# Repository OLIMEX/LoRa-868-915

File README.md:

# LoRa868 / LoRa915 / MOD-LoRa868 / MOD-LoRa915

LoRa modules with SX1276 modem from Semtech.

Product page: https://www.olimex.com/Products/IoT/LoRa/LoRa868/open-source-hardware

Product page: https://www.olimex.com/Products/IoT/LoRa/LoRa915/open-source-hardware

Product page: https://www.olimex.com/Products/IoT/LoRa/MOD-LoRa868/open-source-hardware

Product page: https://www.olimex.com/Products/IoT/LoRa/MOD-LoRa915/open-source-hardware

## License
* Hardware design is released under CERN OHL v1.2 license
* Software is released under GPL3 License
* Documentation is released under CC BY-SA 3.0

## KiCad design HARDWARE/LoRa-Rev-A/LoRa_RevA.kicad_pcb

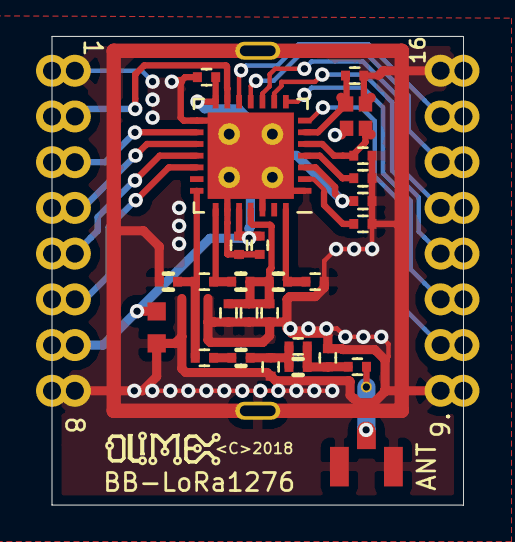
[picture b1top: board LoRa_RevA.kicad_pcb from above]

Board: 2 copper layers, 22.9 x 26.0 mm, 31 parts (0 on the bottom side), 25 nets.

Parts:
C1, C2: 15pF; C_0402_5MIL_DWS
C3, C4, C5, C6, C20: 100nF; C_0402_5MIL_DWS
C7, C8, C16, C21: 47pF; C_0402_5MIL_DWS
C9: 33pF; C_0402_5MIL_DWS
C10: 22uF; C_0603_5MIL_DWS
C11: 4.7pF; C_0402_5MIL_DWS
C12: 1.2pF; C_0402_5MIL_DWS
C13: 1.8pF; C_0402_5MIL_DWS
C19: 2.2pF; C_0402_5MIL_DWS
C25: n.a. (2.2pF); C_0402_5MIL_DWS
C36: 10nF; C_0402_5MIL_DWS
CON1, CON2: CON8; HN1x8_EDGE
EXT_ANT1: U.FL; U.FL-R-SMT-1
JANT1: TESTPAD; TP_SMD
L1: n.a. (82nH); L_0402_5MIL_DWS
L2: 33nH; L_0402_5MIL_DWS
L3: 6.8nH; L_0402_5MIL_DWS
L4: 10nH; L_0402_5MIL_DWS
L5: 6.2nH; L_0402_5MIL_DWS
SHIELD1: TESTPAD; Shield1620
U1: SX1276; QFN-28_EP_6x6_Pitch0.65mm
X1: 32.000MHz_10ppm; SMD2016_4p

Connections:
/DIO0: CON2.6, U1.8
/DIO1: CON2.5, U1.9
/DIO2: CON2.4, U1.10
/DIO3: CON2.3, U1.11
/DIO4: CON2.2, U1.12
/DIO5: CON1.7, U1.13
/MISO: CON1.5, U1.17
/MOSI: CON1.4, U1.18
/NSS: CON1.3, U1.19
/RESET: CON2.7, U1.7
/SCK: CON1.6, U1.16
GND: C1.2, C2.2, C3.2, C4.2, C5.2, C6.2, C7.1, C8.1, C10.2, C11.2, C13.2, C20.2, C21.2, C25.1, C36.2, CON1.1, CON1.8, CON2.1, CON2.8, EXT_ANT1.2, L3.1, SHIELD1.1, U1.1, U1.15, U1.23, U1.26, U1.29, X1.2, X1.4
unnamed: C1.1, U1.6, X1.1
unnamed: C2.1, U1.5, X1.3
unnamed: C4.1, U1.2
unnamed: C5.1, U1.4
unnamed: C9.1, L4.1
unnamed: C11.1, C12.2, L4.2, L5.1
unnamed: C12.1, C13.1, C16.2, L5.2
unnamed: C16.1, EXT_ANT1.1, JANT1.1
unnamed: C9.2, C19.1, L3.2, U1.21
unnamed: C19.2, L2.1, U1.22
unnamed: C25.2, L1.1, U1.28
unnamed: C7.2, C8.2, C36.1, L1.2, L2.2, U1.25
VAA: C3.1, C6.1, C10.1, C20.1, C21.1, CON1.2, U1.3, U1.14, U1.24

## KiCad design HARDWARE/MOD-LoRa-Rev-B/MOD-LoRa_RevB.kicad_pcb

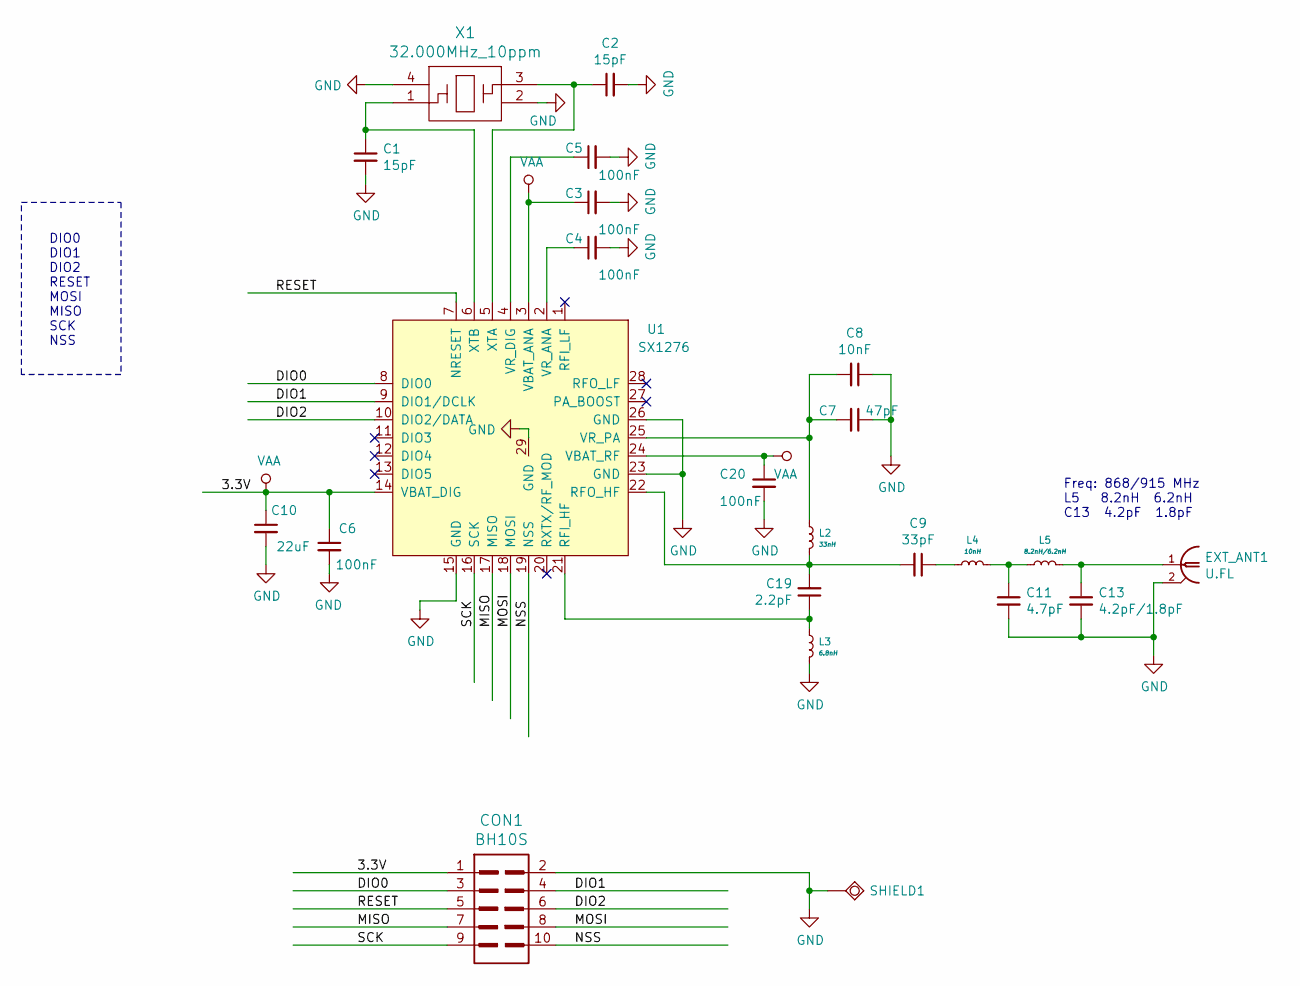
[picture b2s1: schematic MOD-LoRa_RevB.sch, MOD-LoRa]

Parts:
C1, C2: 15pF; C_0402_5MIL_DWS
C3, C4, C5, C6, C20: 100nF; C_0402_5MIL_DWS
C7: 47pF; C_0402_5MIL_DWS
C8: 10nF; C_0402_5MIL_DWS
C9: 33pF; C_0402_5MIL_DWS
C10: 22uF; C_0603_5MIL_DWS
C11: 4.7pF; C_0402_5MIL_DWS
C13: 4.2pF/1.8pF; C_0402_5MIL_DWS
C19: 2.2pF; C_0402_5MIL_DWS
CON1: BH10S; UEXTF
EXT_ANT1: U.FL; U.FL-R-SMT-1
L2: 33nH; L_0402_5MIL_DWS
L3: 6.8nH; L_0402_5MIL_DWS
L4: 10nH; L_0402_5MIL_DWS
L5: 8.2nH/6.2nH; L_0402_5MIL_DWS
SHIELD1: TESTPAD; Shield1620
U1: SX1276; QFN-28_EP_6x6_Pitch0.65mm
X1: 32.000MHz_10ppm; SMD2016_4p

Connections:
/DIO0: CON1.3, U1.8 (DIO0)
/DIO1: CON1.4, U1.9 (DIO1/DCLK)
/DIO2: CON1.6, U1.10 (DIO2/DATA)
/MISO: CON1.7, U1.17 (MISO)
/MOSI: CON1.8, U1.18 (MOSI)
/NSS: CON1.10, U1.19 (NSS)
/RESET: CON1.5, U1.7 (NRESET)
/SCK: CON1.9, U1.16 (SCK)
GND: C1.2, C2.2, C3.2, C4.2, C5.2, C6.2, C7.1, C8.1, C10.2, C11.2, C13.2, C20.2, CON1.2, EXT_ANT1.2, EXT_ANT1.3, EXT_ANT1.4, EXT_ANT1.5, L3.1, SHIELD1.1, U1.15 (GND), U1.23 (GND), U1.26 (GND), U1.29 (GND), X1.2, X1.4
unnamed: C1.1, U1.6 (XTB), X1.1
unnamed: C2.1, U1.5 (XTA), X1.3
unnamed: C4.1, U1.2 (VR_ANA)
unnamed: C5.1, U1.4 (VR_DIG)
unnamed: C7.2, C8.2, L2.2, U1.25 (VR_PA)
unnamed: C9.1, L4.1
unnamed 15: C11.1, L4.2, L5.1; also elsewhere on the board
unnamed 16: C13.1, EXT_ANT1.1, L5.2; also elsewhere on the board
unnamed: C19.1, L3.2, U1.21 (RFI_HF)
unnamed: C9.2, C19.2, L2.1, U1.22 (RFO_HF)
VAA: C3.1, C6.1, C10.1, C20.1, CON1.1, U1.3 (VBAT_ANA), U1.14 (VBAT_DIG), U1.24 (VBAT_RF)

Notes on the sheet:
DIO0 DIO1 DIO2 RESET MOSI MISO SCK NSS
Freq: 868/915 MHz L5 8.2nH 6.2nH C13 4.2pF 1.8pF

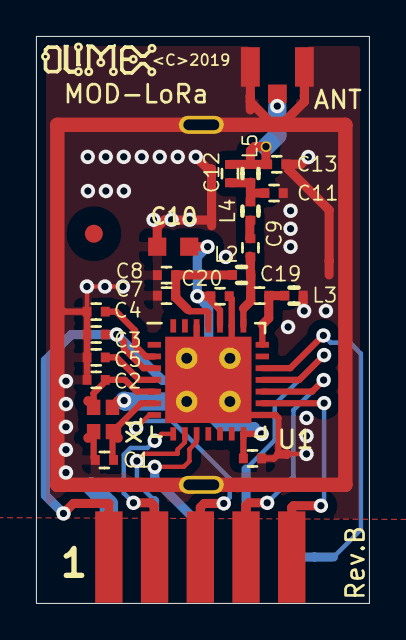
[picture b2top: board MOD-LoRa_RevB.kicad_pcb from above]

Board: 2 copper layers, 18.5 x 31.5 mm, 26 parts (0 on the bottom side), 20 nets.

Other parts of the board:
C12: 1.2pF; C_0402_5MIL_DWS
JANT1: TESTPAD; TP_SMD
Ref*: Val**; Fiducial1x3_transp

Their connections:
unnamed 15: C12.2; also elsewhere on the board
unnamed 16: C12.1, JANT1.1; also elsewhere on the board

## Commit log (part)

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2021-06-30 upload KiCad and User Manual
2021-07-06 Formatting improvements
2021-11-23 updated pictures
2022-05-04 Update
    Added revision A files
2022-05-05 Update
    Added PDF export
2022-11-18 Update
    Demo implementation
2023-10-10 LoRa examples update
    Fixed the issue with the limited range of communication between sender and receiver modules.
2023-10-10 Update README.md
    Updated the interval value and the baudrate of the terminal.
2026-05-28 Update
    Instructions for usage with TTN (TheThingsNetwork) and ChirpStack
2026-06-01 Update
    Updated links to resources
